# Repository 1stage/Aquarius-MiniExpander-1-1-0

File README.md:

# Aquarius Mini Expander 1-1-0
Aquarius Mini Expander 1-1-0 - Rev C, 14 FEB 2021
 
by Sean P. Harrington, sph@1stage.com, http://aquarius.1stage.com
 
## Background
Since the Aquarius doesn't do much on it's own, and playing games on the chicklet keyboard is annoying, adding the functionality of the Mini Expander is essential. The Mini Expander expands the sounds to three voices, adds both a RAM and cartridge ROM expansion slot, and has ports for the Aquarius control pads. But since many Aquarius users DON'T have easy access to these devices, particularly in Europe, it was essential that this PCB be made available. 

## Purpose
The purpose of this project is to document the stock Aquarius Mini Expander, both in schematic form and in board layout. An excellent document from Radofin exists that records the original schematic for the device, and it was used to verify the components and layout of this project, but there are a few, minor discrepancies that have been corrected based on ACTUAL board layout. 

Also, this board serves as a useful prototype for how the expansion bus can be used on the Aquarius. By observing how the AY-3-8910 sound/IO chip is interfaced to the address and data bus, users who want to create their own expansion device could do so. Since it is already a very simple device (only about 25 components), the large footprint of the board could be improved through smaller SMD components and better trace routing, leaving plenty of room for additional functionality within the original (or modified) Mini Expander case.

To that end, an additional header for AY-3-8910 I/O has been added, along with detailed silkscreen markings on both the new header and the upper Expansion Slot so that hobbyists can experiment with creating their own expansions to the Aquarius. A reminder that the Expansion Slot pins are NOT like GPIO pins on an Arduino or Raspberry Pi. A0 does NOT mean analog pin zero, and D0 does NOT mean digital pin zero (nor any of the others). If you want to create your own I/O procedures, use the IO pins on the AY-3-8910 instead.

## Bill of Materials
https://docs.google.com/spreadsheets/d/1Fgy7V73wTicvzhZblFc1MAg1R4uz7tYPBy140xyRtXA	

## Components
* Aquarius Mini Expander v1-1-0 PCB Rev B, 09 SEP 2020
* Electronic components (listed in BOM above)
* 3D printed parts
  * Aquarius Mini Expander v1-1-0 case BOTTOM
  * Aquarius Mini Expander v1-1-0 case TOP (in development)
  * Aquarius Mini Expander v1-1-0 case TRAP_FRONT (in development)
  * Aquarius Mini Expander v1-1-0 case TRAP_REAR (in development)
* Assembly screws (to be specified later)
* Trap Door springs (to be specified later)
* Trap Door hinges (to be specified later)

## Caveats
* This project does **not incorporate** any new functionality. Users who want to add functionality may fork this project on their own.
  * SD Card read/write is not implemented, such as on the Micro Expander, a project developed by Bruce Abbott
  * A RAM expansion device is not included, such as the 32kb RAM Cartridge, a product developed by Jay Snellen, III
  * A cartridge ROM expansion device is not included, such as the AquariCart, a product developed by Jay Snellen, III
  * Switchable use of ATARI or SEGA joysticks (despite the same DB9 plugs)
* For users who want to use RAM or ROM in either cartridge slot, jumper pads (solder) have been added to connect pin 34 (rear slot) and/or pin 44 (front slot) to GND. Use this at your own discretion, but understand that you can't insert two ROM cartridges and expect them to work. Using two RAM cartridges could theoretically work, but it has not been tested.
* To maintain original layout, the three interconnect wires are not incorporated into the PCB. They are indicated as "WIRE" on the PCB, which should be bridged with 22 gauge solid core, insulated wire.
* The L1 choke/line filter (33uH) is difficult to source. Users may simply bridge this gap with 22 gauge solid core wire, or they can use a 0 ohm ferrite bead.
* Two of the small Control Pad interface boards are included as breakaways on either side of the narrow part of the board. These must be removed before the Mini Expander PCB can fit in the stock plastic shell. These small interface boards are used to transition the nine wires in the joystick cable to the mylar conductive pad used in the Control Pads.

## FAQs
* Where can I get the PCBs?
  * https://www.pcbway.com/project/shareproject/Aquarius_Computer_Mini_Expander_PCB.html
* Will you build me a Mini Expander? I'll pay you!
  * I won't (WAY too much to do), but it's not too difficult to do yourself. Also, there are some in the Aquarius community who can build one for you.
* Where can I get a case for this?
  * 3D print one yourself by exploring the 3d folder of the project. I haven't had time to create the top half (there are some intricate trap-door things to model), but maybe someone in the community will model one to fit?
* What about Control Pads?
  * There is a prototype for the Control Pads within the project, but I haven't had the time to take it beyond the prototype phase. This is open source, so have at it!
* How is this project different from the Micro Expander?
  * Designed by Bruce Abbott, the Aquarius Micro Expander is similar to the Mini Expander in that it has an AY-3-8910 sound chip and a header for Control Pad input (NOT joystick ports, a pin header). The Micro Expander is different in that it has a 32k memory expansion in it, a USB port, a 3.5mm audio port, along with a custom ROM that features a PT3 music player, USB ROM reading access, and a customized version of BASIC. The down side is that it blocks the Expansion Port of the Aquarius, so cartridge-based ROM programs (SNAFU, Nightstalker, D&D etc.) can't be used (unless you have the ROM image to load through USB).
* Why can't I use the A00-A15 expansion pins as analog input/output, or the D00-D15 as digital input/output for my Arduino experiments?
  * First of all, these pins are NOT analog and digital input/output pins! They are DIRECTLY connected to the **address** bus and the **data** bus (hence the A00 or D00 markings). Unless you know how the timings of these busses work, you're more than likely going to damage your Aquarius. If you want to experiment safely with TTL level inputs and outputs, use the IOA0-IOA7 or IOB0-IOB7 pins on the AY-3-8910 header instead.

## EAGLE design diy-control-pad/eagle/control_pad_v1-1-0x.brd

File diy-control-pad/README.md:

# DIY Aquarius Control Pad 1-1-0x
DIY Aquarius Control Pad 1-1-0x, 11 OCT 2020
 
by Sean P. Harrington, sph@1stage.com, http://aquarius.1stage.com
 
## Purpose
While reverse engineering the Mini Expander, it became obvious very quickly that there was also a need for easy-to-make Control Pads for the Aquarius. Those, as many of my UK/EU friends have said, are rare as hen's teeth. The stock unit was designed to be SUPER cheap and SUPER easy to crank out in quantity, however, the processes used in making the conductive ink, flexible control boards for the joysticks are not easily recreatable by a casual maker or electronics enthusiast. So I designed these "fugly" control boards using inexpensive, easy to source through-hole tactile switches and LN4148 diodes, a PCB, and a commonly available Atari/Sega joystick extension cable. 

## Components
* DIY Aquarius Control Pad v1-1-0x PCB, 11 OCT 2020
* Electronic components
  * 22 @ 6mm through hole tactile switches
  * 42 @ 1N4148 diodes
* 6 foot / 2 meter Atari/Sega Joystick extension cable
* 3D printed parts
  * DIY Aquarius Control Pad v1-1-0x BASE
  * DIY Aquarius Control Pad v1-1-0x TOP
  * DIY Aquarius Control Pad v1-1-0x DISC
  * DIY Aquarius Control Pad v1-1-0x BUTTONS
* Assembly screws (to be specified later)

## Caveats
* None, right now...

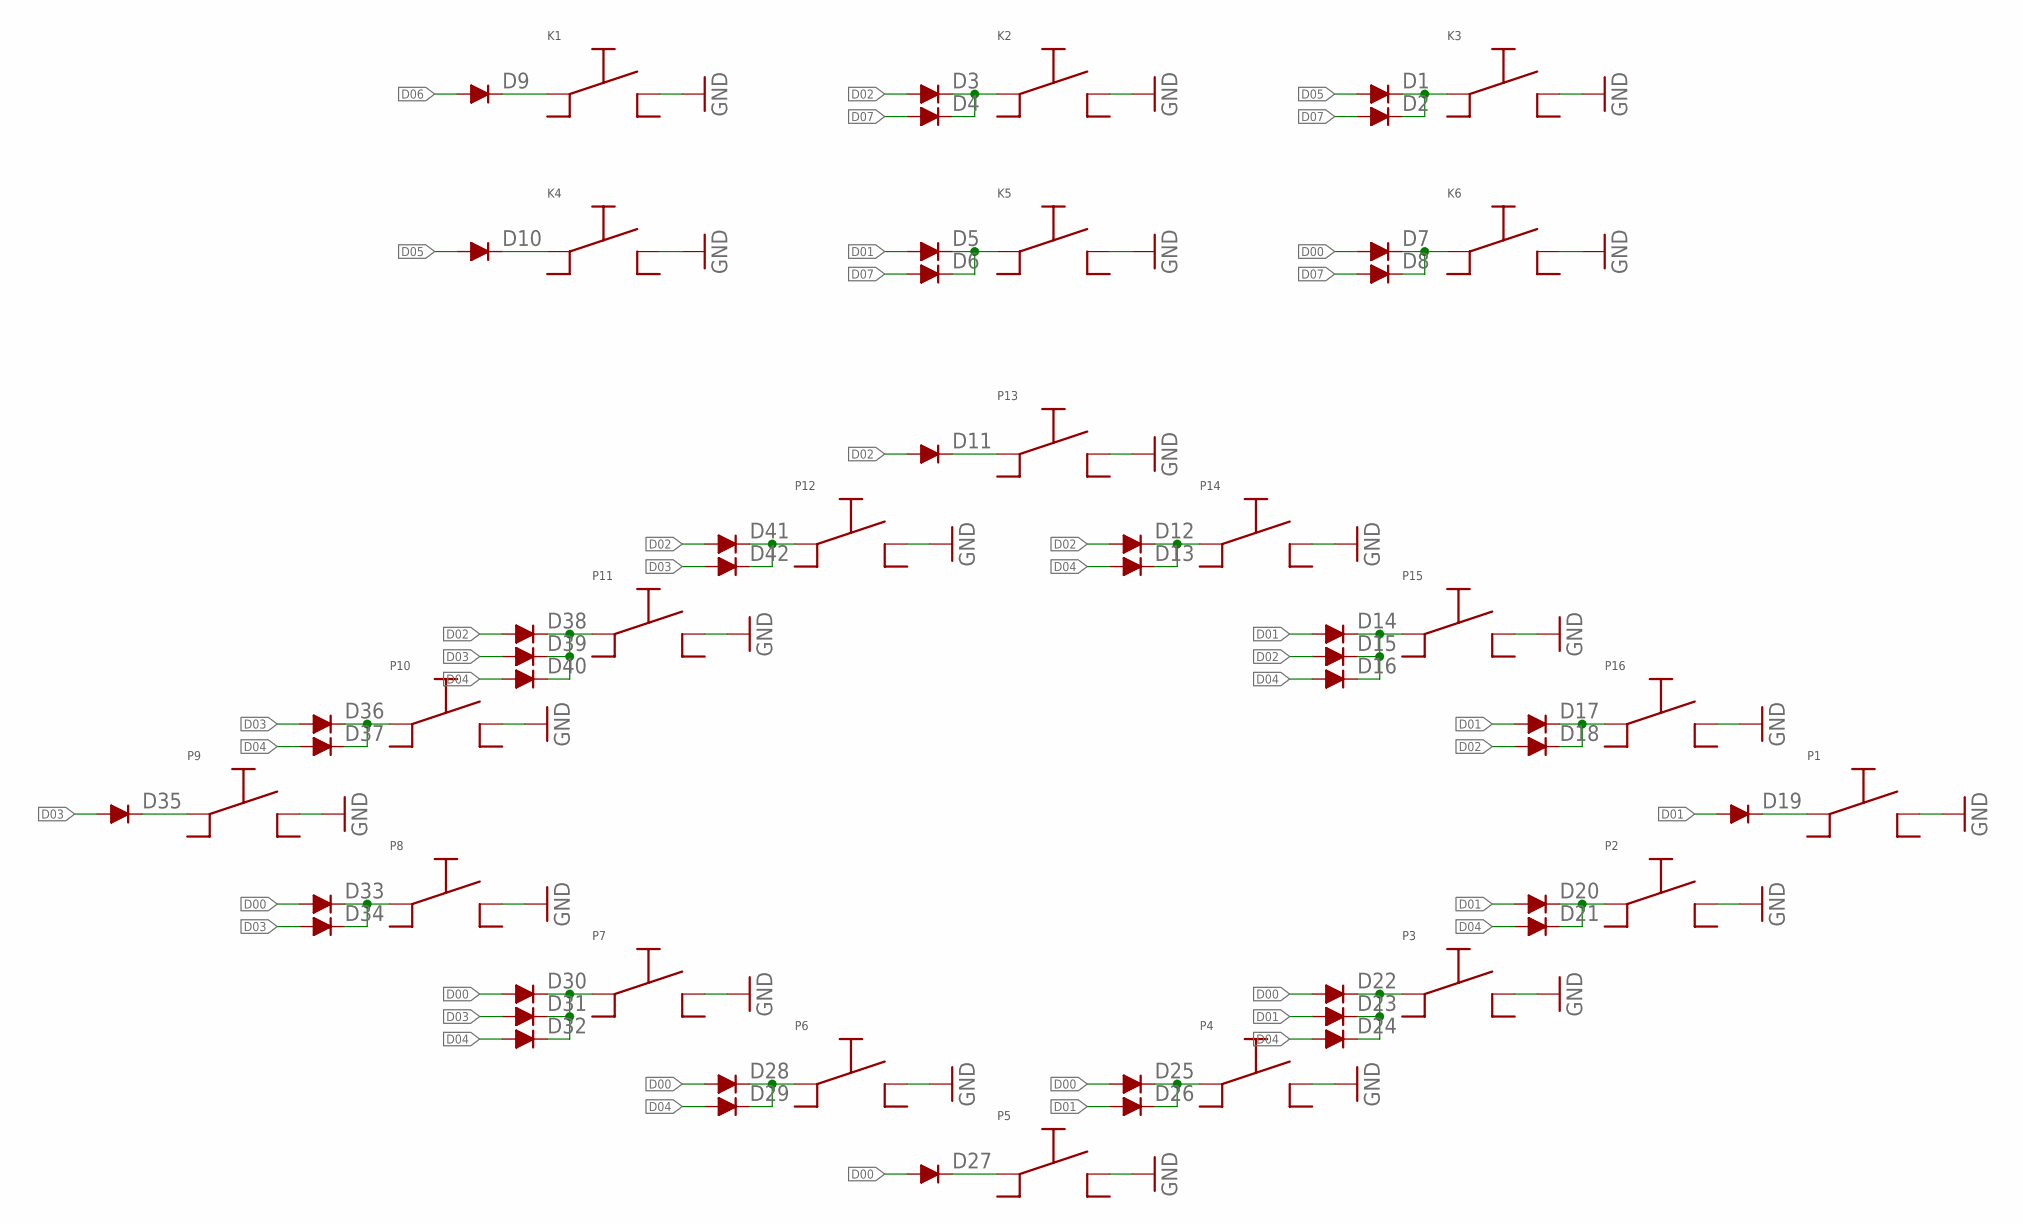
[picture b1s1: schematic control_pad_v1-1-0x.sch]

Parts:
D1, D2, D3, D4, D5, D6, D7, D8, D9, D10, D11, D12, D13, D14, D15, D16, D17, D18, D19, D20, D21, D22, D23, D24, D25, D26, D27, D28, D29, D30, D31, D32, D33, D34, D35, D36, D37, D38, D39, D40, D41, D42: 1N4148; DO35-10
K1, K2, K3, K4, K5, K6: TACT-SPST
P1, P2, P3, P4, P5, P6, P7, P8, P9, P10, P11, P12, P13, P14, P15, P16: TACT-SPST

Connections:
D00: D7.A, D22.A, D25.A, D27.A, D28.A, D30.A, D33.A
D01: D5.A, D14.A, D17.A, D19.A, D20.A, D23.A, D26.A
D02: D3.A, D11.A, D12.A, D15.A, D18.A, D38.A, D41.A
D03: D31.A, D34.A, D35.A, D36.A, D39.A, D42.A
D04: D13.A, D16.A, D21.A, D24.A, D29.A, D32.A, D37.A, D40.A
D05: D1.A, D10.A
D06: D9.A
D07: D2.A, D4.A, D6.A, D8.A
GND: K1.P$2, K1.P$4, K2.P$2, K2.P$4, K3.P$2, K3.P$4, K4.P$2, K4.P$4, K5.P$2, K5.P$4, K6.P$2, K6.P$4, P1.P$2, P1.P$4, P2.P$2, P2.P$4, P3.P$2, P3.P$4, P4.P$2, P4.P$4, P5.P$2, P5.P$4, P6.P$2, P6.P$4, P7.P$2, P7.P$4, P8.P$2, P8.P$4, P9.P$2, P9.P$4, P10.P$2, P10.P$4, P11.P$2, P11.P$4, P12.P$2, P12.P$4, P13.P$2, P13.P$4, P14.P$2, P14.P$4, P15.P$2, P15.P$4, P16.P$2, P16.P$4
unnamed: D9.C, K1.P$1, K1.P$3
unnamed: D10.C, K4.P$1, K4.P$3
unnamed: D11.C, P13.P$1, P13.P$3
unnamed: D1.C, D2.C, K3.P$1, K3.P$3
unnamed: D3.C, D4.C, K2.P$1, K2.P$3
unnamed: D5.C, D6.C, K5.P$1, K5.P$3
unnamed: D7.C, D8.C, K6.P$1, K6.P$3
unnamed: D14.C, D15.C, D16.C, P15.P$1, P15.P$3
unnamed: D12.C, D13.C, P14.P$1, P14.P$3
unnamed: D19.C, P1.P$1, P1.P$3
unnamed: D17.C, D18.C, P16.P$1, P16.P$3
unnamed: D20.C, D21.C, P2.P$1, P2.P$3
unnamed: D22.C, D23.C, D24.C, P3.P$1, P3.P$3
unnamed: D25.C, D26.C, P4.P$1, P4.P$3
unnamed: D27.C, P5.P$1, P5.P$3
unnamed: D28.C, D29.C, P6.P$1, P6.P$3
unnamed: D30.C, D31.C, D32.C, P7.P$1, P7.P$3
unnamed: D33.C, D34.C, P8.P$1, P8.P$3
unnamed: D35.C, P9.P$1, P9.P$3
unnamed: D36.C, D37.C, P10.P$1, P10.P$3
unnamed: D38.C, D39.C, D40.C, P11.P$1, P11.P$3
unnamed: D41.C, D42.C, P12.P$1, P12.P$3

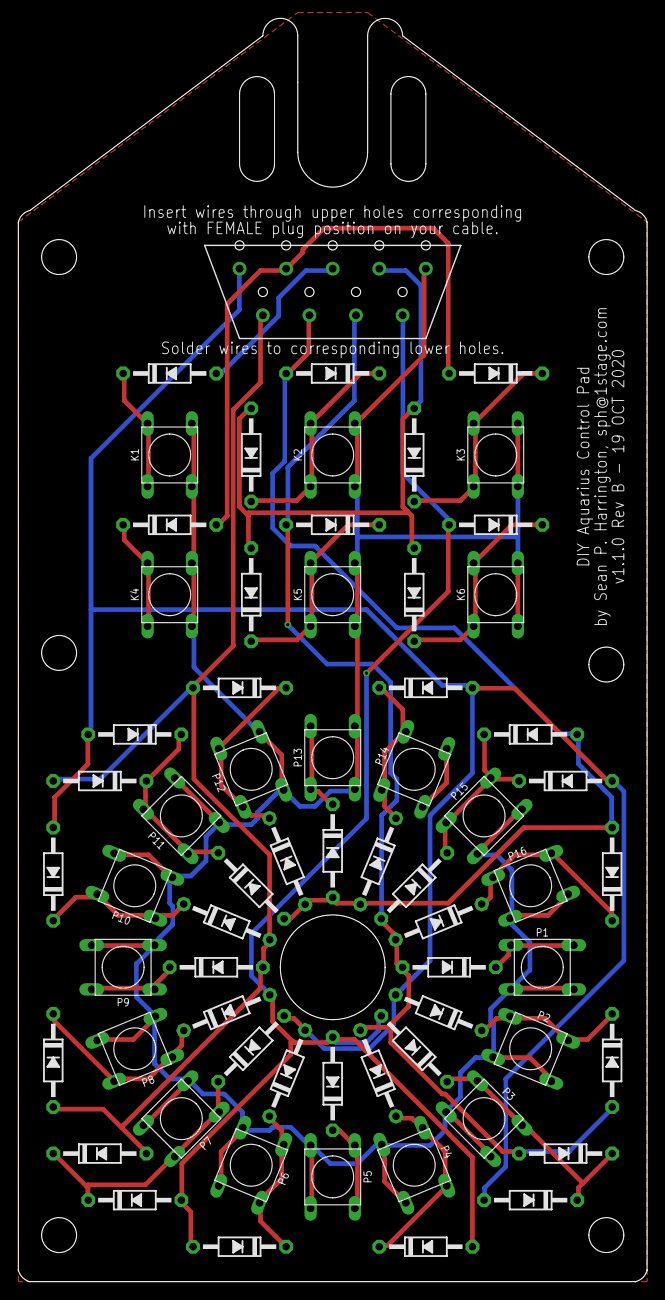
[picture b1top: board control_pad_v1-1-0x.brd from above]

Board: 2 copper layers, 68.6 x 137.8 mm, 64 parts (0 on the bottom side), 30 nets.

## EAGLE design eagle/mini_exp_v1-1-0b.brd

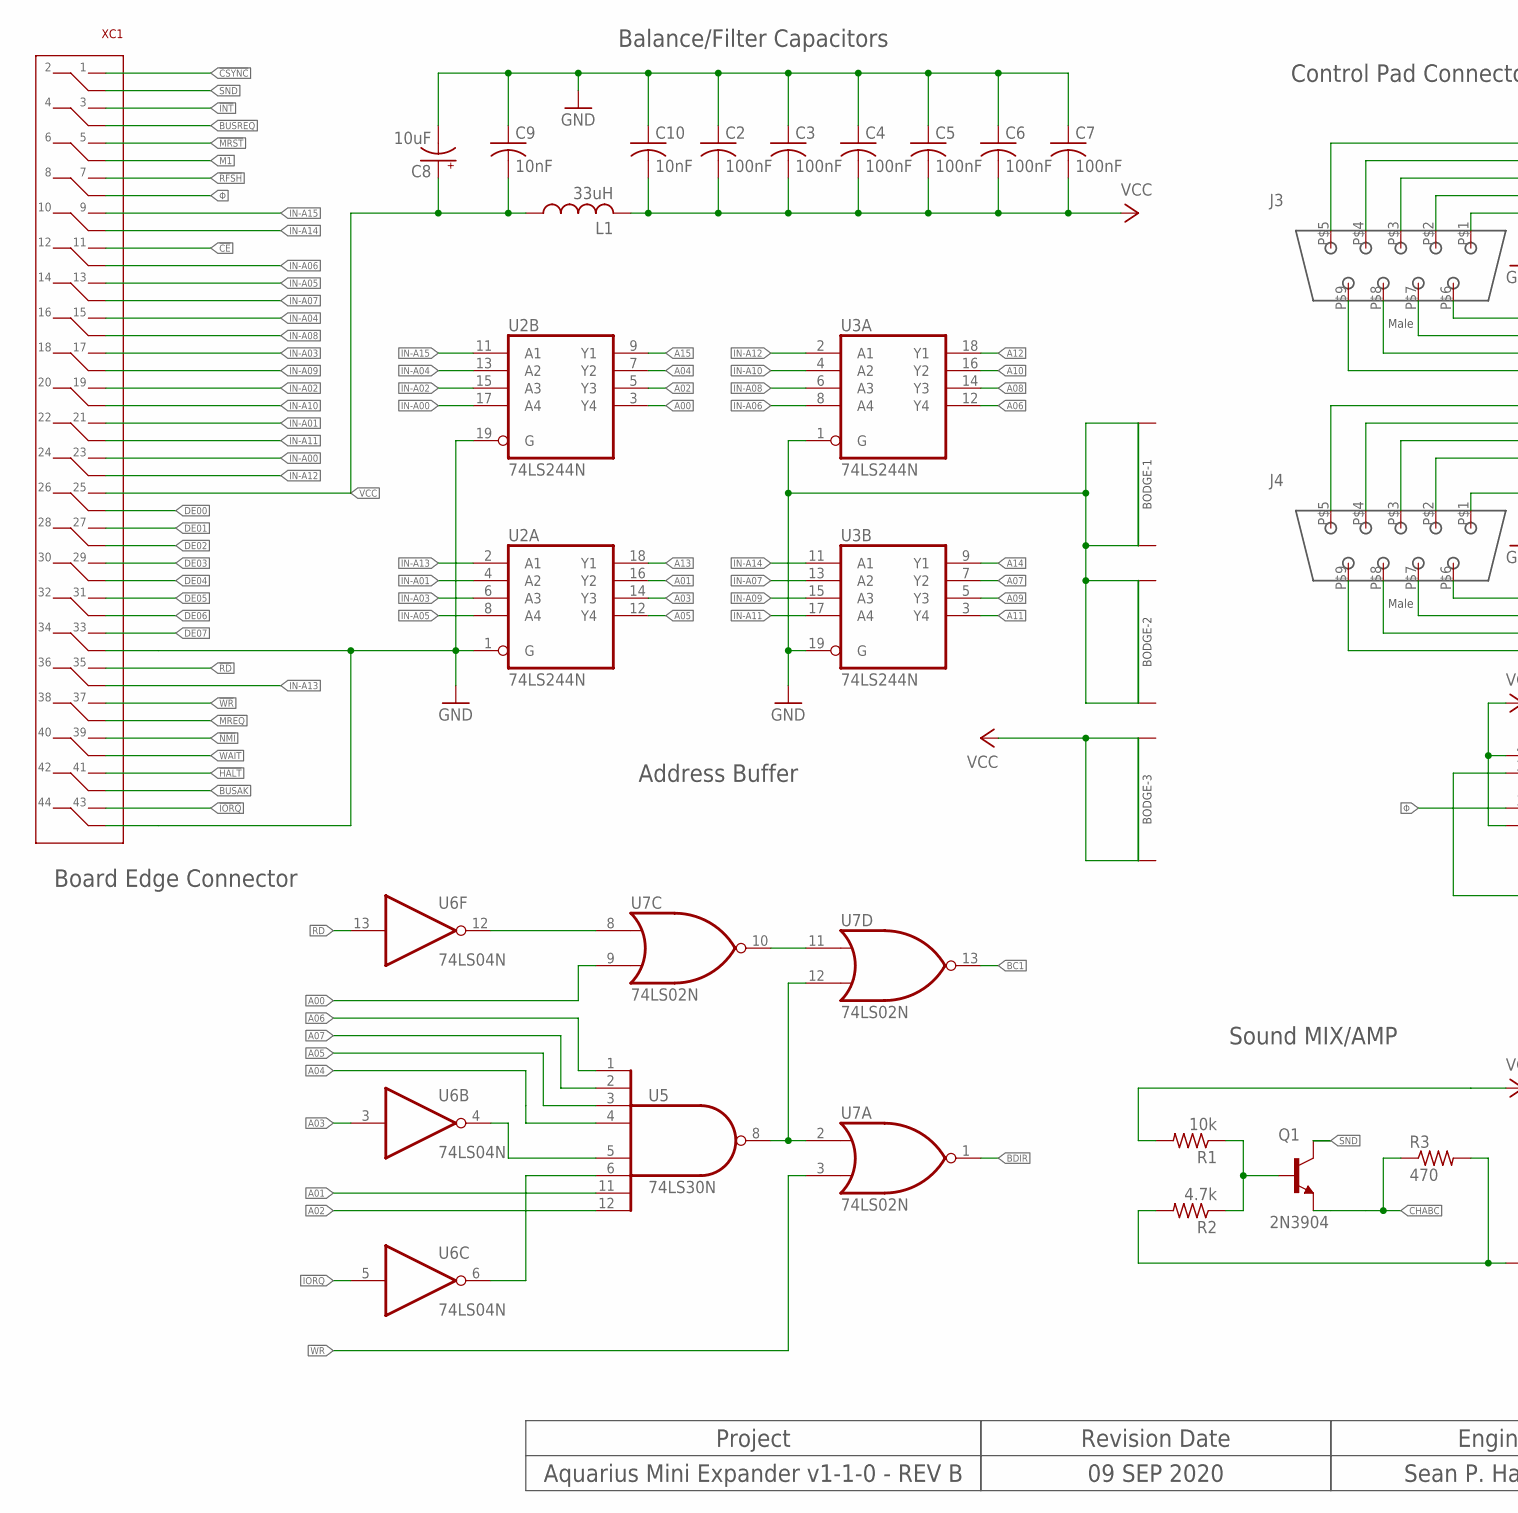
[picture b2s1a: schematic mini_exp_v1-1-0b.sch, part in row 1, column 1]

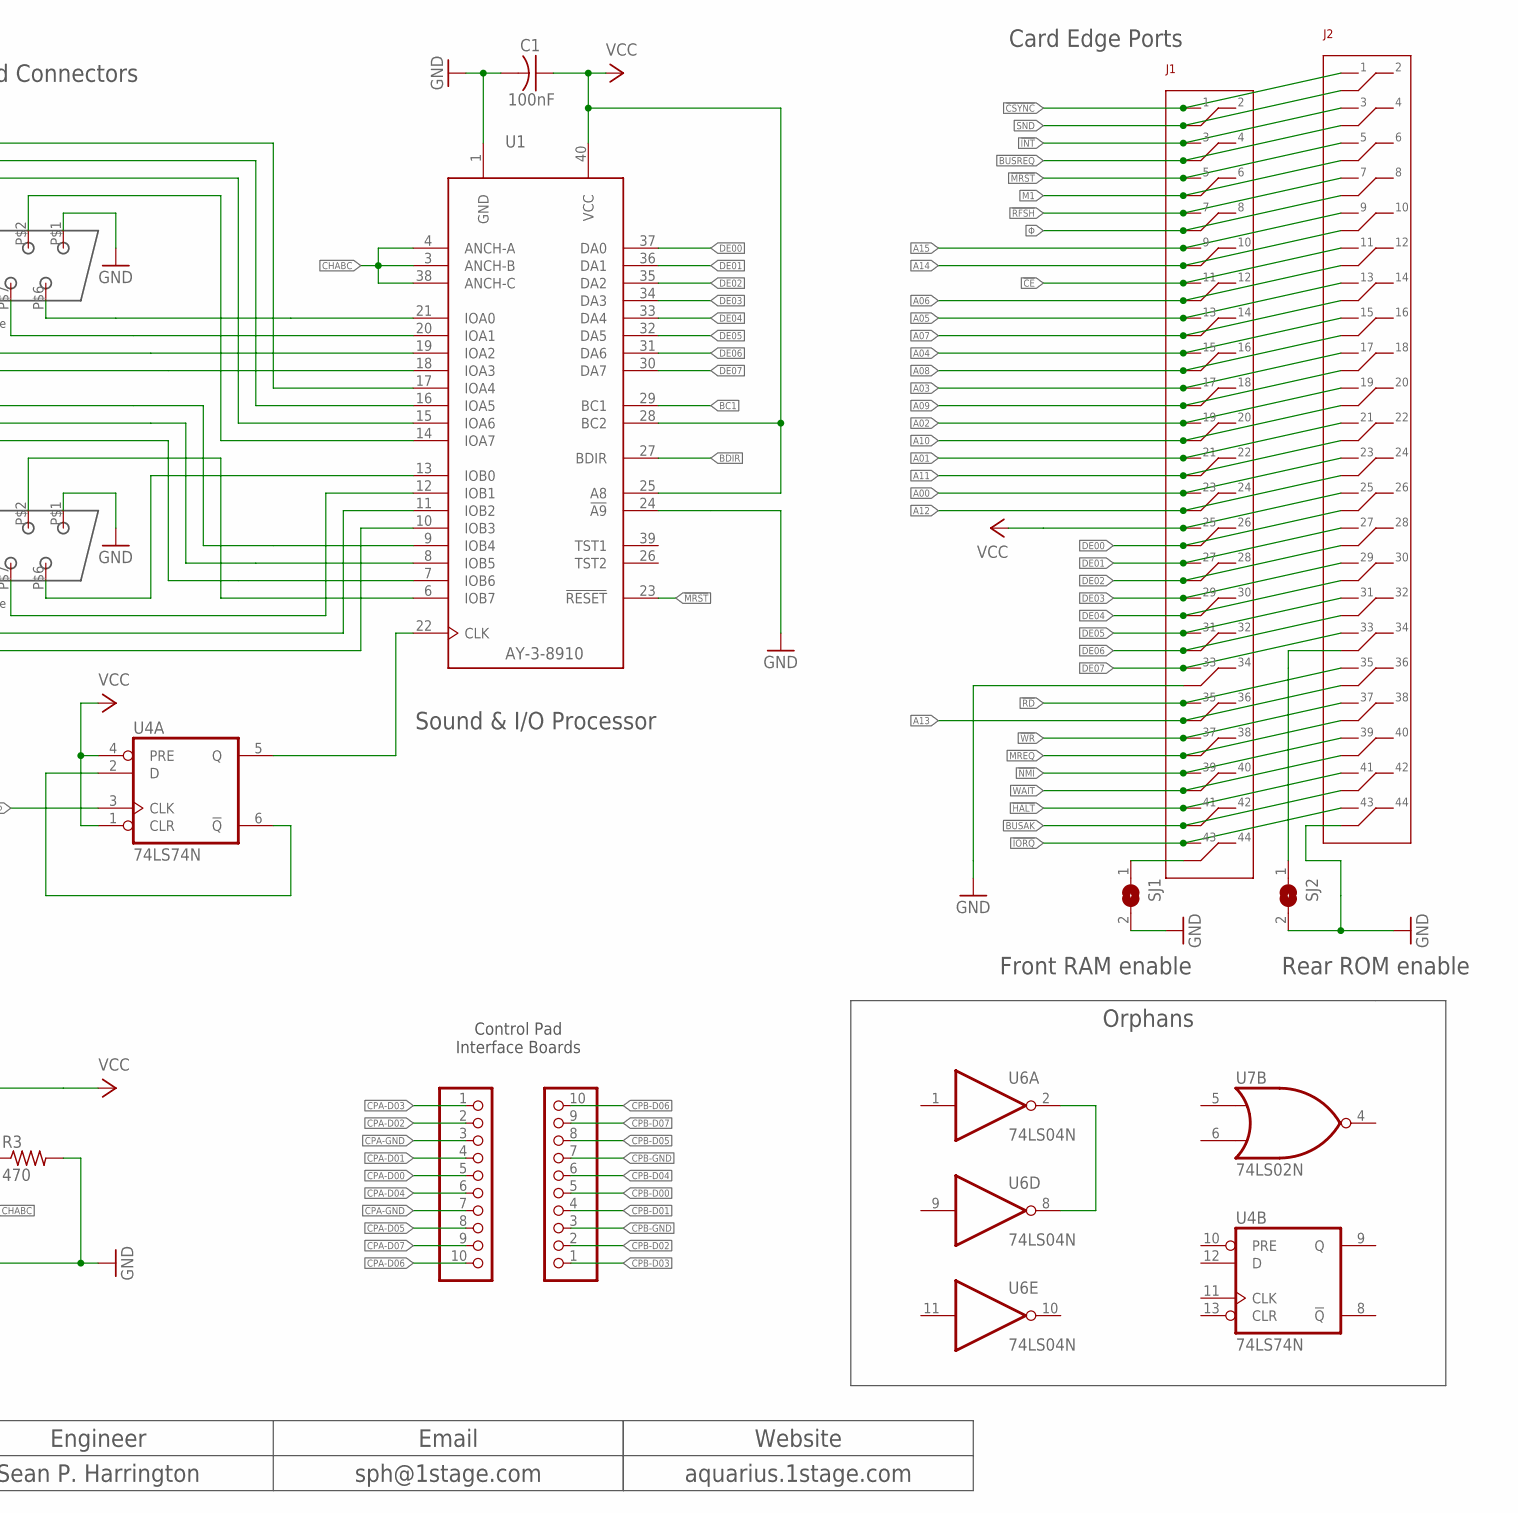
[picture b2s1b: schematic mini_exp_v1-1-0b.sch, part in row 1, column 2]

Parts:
C1, C2, C3, C4, C5, C6, C7: 100nF; C050-025X095
C8: 10uF; E22-6
C9, C10: 10nF; C075-032X103
J1, J2: CR22A-44D-2.54DS(70)STRAIGHT; CR22A-44D-2.54DS(70)
J3, J4: DB9-MALE-RA
JP1, JP2: PINHD-1X10; 1X10
L1: 33uH; 0204/5
Q1: 2N3904; TO92
R1: 10k; 0207/7
R2: 4.7k; 0207/7
R3: 470; 0207/7
SJ1, SJ2: SJ
U1: AY-3-8910; RAD38910-DIL40-6
U2, U3: 74LS244N; DIL20
U4: 74LS74N; DIL14
U5: 74LS30N; DIL14
U6: 74LS04N; DIL14
U7: 74LS02N; DIL14
XC1: AQ-CART-EDGE
XX01: AQ-MX-BODGE-1
XX02: AQ-MX-BODGE-2
XX03: AQ-MX-BODGE-3

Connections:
!BUSAK: J1.P$42 (X42), J2.P$42 (X42), XC1.P$42 (X42)
!BUSREQ: J1.P$4 (X4), J2.P$4 (X4), XC1.P$4 (X4)
!CE: J1.P$11 (X11), J2.P$11 (X11), XC1.P$11 (X11)
!CSYNC: J1.P$1 (X1), J2.P$1 (X1), XC1.P$1 (X1)
!HALT: J1.P$41 (X41), J2.P$41 (X41), XC1.P$41 (X41)
!INT: J1.P$3 (X3), J2.P$3 (X3), XC1.P$3 (X3)
!IORQ: J1.P$43 (X43), J2.P$43 (X43), U6.5 (I), XC1.P$43 (X43)
!M1: J1.P$6 (X6), J2.P$6 (X6), XC1.P$6 (X6)
!MREQ: J1.P$38 (X38), J2.P$38 (X38), XC1.P$38 (X38)
!MRST: J1.P$5 (X5), J2.P$5 (X5), U1.23 (!RESET), XC1.P$5 (X5)
!NMI: J1.P$39 (X39), J2.P$39 (X39), XC1.P$39 (X39)
!RD: J1.P$35 (X35), J2.P$35 (X35), U6.13 (I), XC1.P$35 (X35)
!RFSH: J1.P$7 (X7), J2.P$7 (X7), XC1.P$7 (X7)
!WAIT: J1.P$40 (X40), J2.P$40 (X40), XC1.P$40 (X40)
!WR: J1.P$37 (X37), J2.P$37 (X37), U7.3 (I1), XC1.P$37 (X37)
A00: J1.P$23 (X23), J2.P$23 (X23), U2.3 (Y4), U7.9 (I1)
A01: J1.P$21 (X21), J2.P$21 (X21), U2.16 (Y2), U5.11 (I6)
A02: J1.P$19 (X19), J2.P$19 (X19), U2.5 (Y3), U5.12 (I7)
A03: J1.P$17 (X17), J2.P$17 (X17), U2.14 (Y3), U6.3 (I)
A04: J1.P$15 (X15), J2.P$15 (X15), U2.7 (Y2), U5.4 (I3)
A05: J1.P$13 (X13), J2.P$13 (X13), U2.12 (Y4), U5.3 (I2)
A06: J1.P$12 (X12), J2.P$12 (X12), U3.12 (Y4), U5.1 (I0)
A07: J1.P$14 (X14), J2.P$14 (X14), U3.7 (Y2), U5.2 (I1)
A08: J1.P$16 (X16), J2.P$16 (X16), U3.14 (Y3)
A09: J1.P$18 (X18), J2.P$18 (X18), U3.5 (Y3)
A10: J1.P$20 (X20), J2.P$20 (X20), U3.16 (Y2)
A11: J1.P$22 (X22), J2.P$22 (X22), U3.3 (Y4)
A12: J1.P$24 (X24), J2.P$24 (X24), U3.18 (Y1)
A13: J1.P$36 (X36), J2.P$36 (X36), U2.18 (Y1)
A14: J1.P$10 (X10), J2.P$10 (X10), U3.9 (Y1)
A15: J1.P$9 (X9), J2.P$9 (X9), U2.9 (Y1)
BC1: U1.29 (BC1), U7.13 (O)
BDIR: U1.27 (BDIR), U7.1 (O)
CHABC: Q1.3 (E), R3.1, U1.3 (ANCH-B), U1.4 (ANCH-A), U1.38 (ANCH-C)
CPA-D00: JP1.5
CPA-D01: JP1.4
CPA-D02: JP1.2
CPA-D03: JP1.1
CPA-D04: JP1.6
CPA-D05: JP1.8
CPA-D06: JP1.10
CPA-D07: JP1.9
CPA-GND: JP1.3, JP1.7
CPB-D00: JP2.5
CPB-D01: JP2.4
CPB-D02: JP2.2
CPB-D03: JP2.1
CPB-D04: JP2.6
CPB-D05: JP2.8
CPB-D06: JP2.10
CPB-D07: JP2.9
CPB-GND: JP2.3, JP2.7
DE00: J1.P$26 (X26), J2.P$26 (X26), U1.37 (DA0), XC1.P$26 (X26)
DE01: J1.P$27 (X27), J2.P$27 (X27), U1.36 (DA1), XC1.P$27 (X27)
DE02: J1.P$28 (X28), J2.P$28 (X28), U1.35 (DA2), XC1.P$28 (X28)
DE03: J1.P$29 (X29), J2.P$29 (X29), U1.34 (DA3), XC1.P$29 (X29)
DE04: J1.P$30 (X30), J2.P$30 (X30), U1.33 (DA4), XC1.P$30 (X30)
DE05: J1.P$31 (X31), J2.P$31 (X31), U1.32 (DA5), XC1.P$31 (X31)
DE06: J1.P$32 (X32), J2.P$32 (X32), U1.31 (DA6), XC1.P$32 (X32)
DE07: J1.P$33 (X33), J2.P$33 (X33), U1.30 (DA7), XC1.P$33 (X33)
GND: C1.2, C2.1, C3.1, C4.1, C5.1, C6.1, C7.1, C8.-, C9.1, C10.1, J1.P$34 (X34), J2.P$44 (X44), J3.P$1, J4.P$1, R2.2, R3.2, SJ1.2, SJ2.2, U1.1 (GND), U1.24 (!A9), U2.1 (G), U2.10 (GND), U2.19 (G), U3.1 (G), U3.10 (GND), U3.19 (G), U4.7 (GND), U5.7 (GND), U6.7 (GND), U7.7 (GND), XC1.P$34 (X34), XC1.P$44 (X44), XX01.P$1, XX01.P$2, XX02.P$1, XX02.P$2
IN-A00: U2.17 (A4), XC1.P$23 (X23)
IN-A01: U2.4 (A2), XC1.P$21 (X21)
IN-A02: U2.15 (A3), XC1.P$19 (X19)
IN-A03: U2.6 (A3), XC1.P$17 (X17)
IN-A04: U2.13 (A2), XC1.P$15 (X15)
IN-A05: U2.8 (A4), XC1.P$13 (X13)
IN-A06: U3.8 (A4), XC1.P$12 (X12)
IN-A07: U3.13 (A2), XC1.P$14 (X14)
IN-A08: U3.6 (A3), XC1.P$16 (X16)
IN-A09: U3.15 (A3), XC1.P$18 (X18)
IN-A10: U3.4 (A2), XC1.P$20 (X20)
IN-A11: U3.17 (A4), XC1.P$22 (X22)
IN-A12: U3.2 (A1), XC1.P$24 (X24)
IN-A13: U2.2 (A1), XC1.P$36 (X36)
IN-A14: U3.11 (A1), XC1.P$10 (X10)
IN-A15: U2.11 (A1), XC1.P$9 (X9)
unnamed: Q1.2 (B), R1.1, R2.1
unnamed: U6.2 (O), U6.8 (O)
unnamed: J1.P$44 (X44), SJ1.1
unnamed: J2.P$34 (X34), SJ2.1
unnamed: J4.P$6, U1.13 (IOB0)
unnamed: U7.10 (O), U7.11 (I0)
unnamed: U4.2 (D), U4.6 (!Q)
unnamed: U1.22 (CLK), U4.5 (Q)
unnamed: U5.8 (O), U7.2 (I0), U7.12 (I1)
unnamed: U6.12 (O), U7.8 (I0)
unnamed: U5.5 (I4), U6.4 (O)
unnamed: U5.6 (I5), U6.6 (O)
unnamed: J4.P$2, U1.6 (IOB7)
unnamed: J4.P$7, U1.12 (IOB1)
unnamed: J4.P$8, U1.11 (IOB2)
unnamed: J4.P$5, U1.9 (IOB4)
unnamed: J4.P$4, U1.8 (IOB5)
unnamed: J4.P$3, U1.7 (IOB6)
unnamed: J4.P$9, U1.10 (IOB3)
unnamed: J3.P$2, U1.14 (IOA7)
unnamed: J3.P$3, U1.15 (IOA6)
unnamed: J3.P$4, U1.16 (IOA5)
unnamed: J3.P$5, U1.17 (IOA4)
unnamed: J3.P$6, U1.21 (IOA0)
unnamed: J3.P$7, U1.20 (IOA1)
unnamed: J3.P$8, U1.19 (IOA2)
unnamed: J3.P$9, U1.18 (IOA3)
SND: J1.P$2 (X2), J2.P$2 (X2), Q1.1 (C), XC1.P$2 (X2)
VCC: C1.1, C2.2, C3.2, C4.2, C5.2, C6.2, C7.2, C8.+, C9.2, C10.2, J1.P$25 (X25), J2.P$25 (X25), L1.1, L1.2, R1.2, U1.25 (A8), U1.28 (BC2), U1.40 (VCC), U2.20 (VCC), U3.20 (VCC), U4.1 (CLR), U4.4 (PRE), U4.14 (VCC), U5.14 (VCC), U6.14 (VCC), U7.14 (VCC), XC1.P$25 (X25), XX03.P$1, XX03.P$2
Φ: J1.P$8 (X8), J2.P$8 (X8), U4.3 (CLK), XC1.P$8 (X8)

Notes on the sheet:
Orphans
Board Edge Connector
Card Edge Ports
Control Pad Connectors
Sound & I/O Processor
Sound MIX/AMP
Address Buffer
Balance/Filter Capacitors
Aquarius Mini Expander v1-1-0 - REV B
Project
09 SEP 2020
Revision Date
Sean P. Harrington
Engineer
aquarius.1stage.com
Website
Email
sph@1stage.com
Front RAM enable
Rear ROM enable
Control Pad Interface Boards

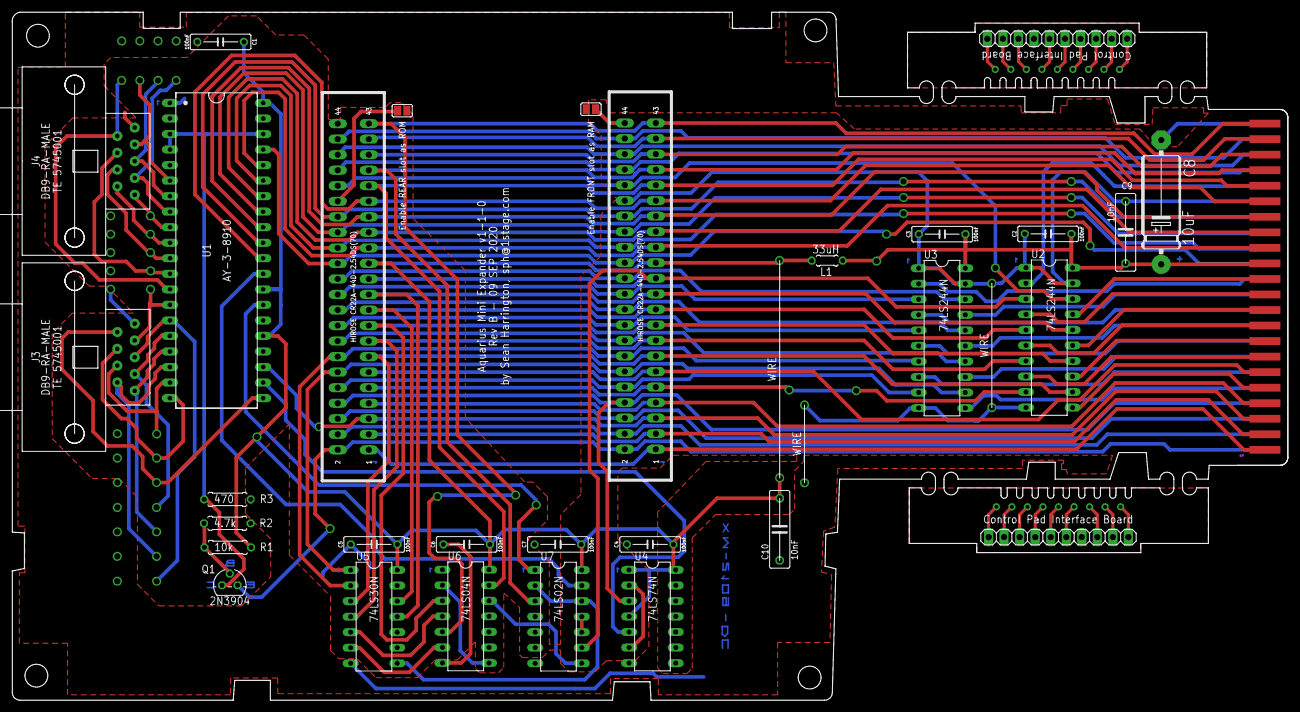
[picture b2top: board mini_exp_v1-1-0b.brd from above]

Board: 2 copper layers, 208.6 x 112.5 mm, 34 parts (0 on the bottom side), 91 nets.

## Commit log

2020-08-27 First full push
2020-09-03 Post PCB check edits
2020-09-03 Clean up
2020-09-03 Clean up, post PCB arrival
2020-09-09 Added Control Pad interface boards, updated board PDF, updated schematic PDF
2020-09-28 Post-launch clean up
2020-09-28 Added images folder
2020-09-28 Updated STL file for MM units (Cura default)
2020-10-05 Another update
2020-10-14 Added DIY Control Paad
2020-10-14 Fixed DIY Control Pad file naming
2020-10-14 Adding the obligatory PDF documentation
2020-10-14 Organize files into folders
2020-10-15 set default units to mm
2021-02-08 Post publishing clean up, Add Rev C
2021-02-09 Added IO Header to Rev C
